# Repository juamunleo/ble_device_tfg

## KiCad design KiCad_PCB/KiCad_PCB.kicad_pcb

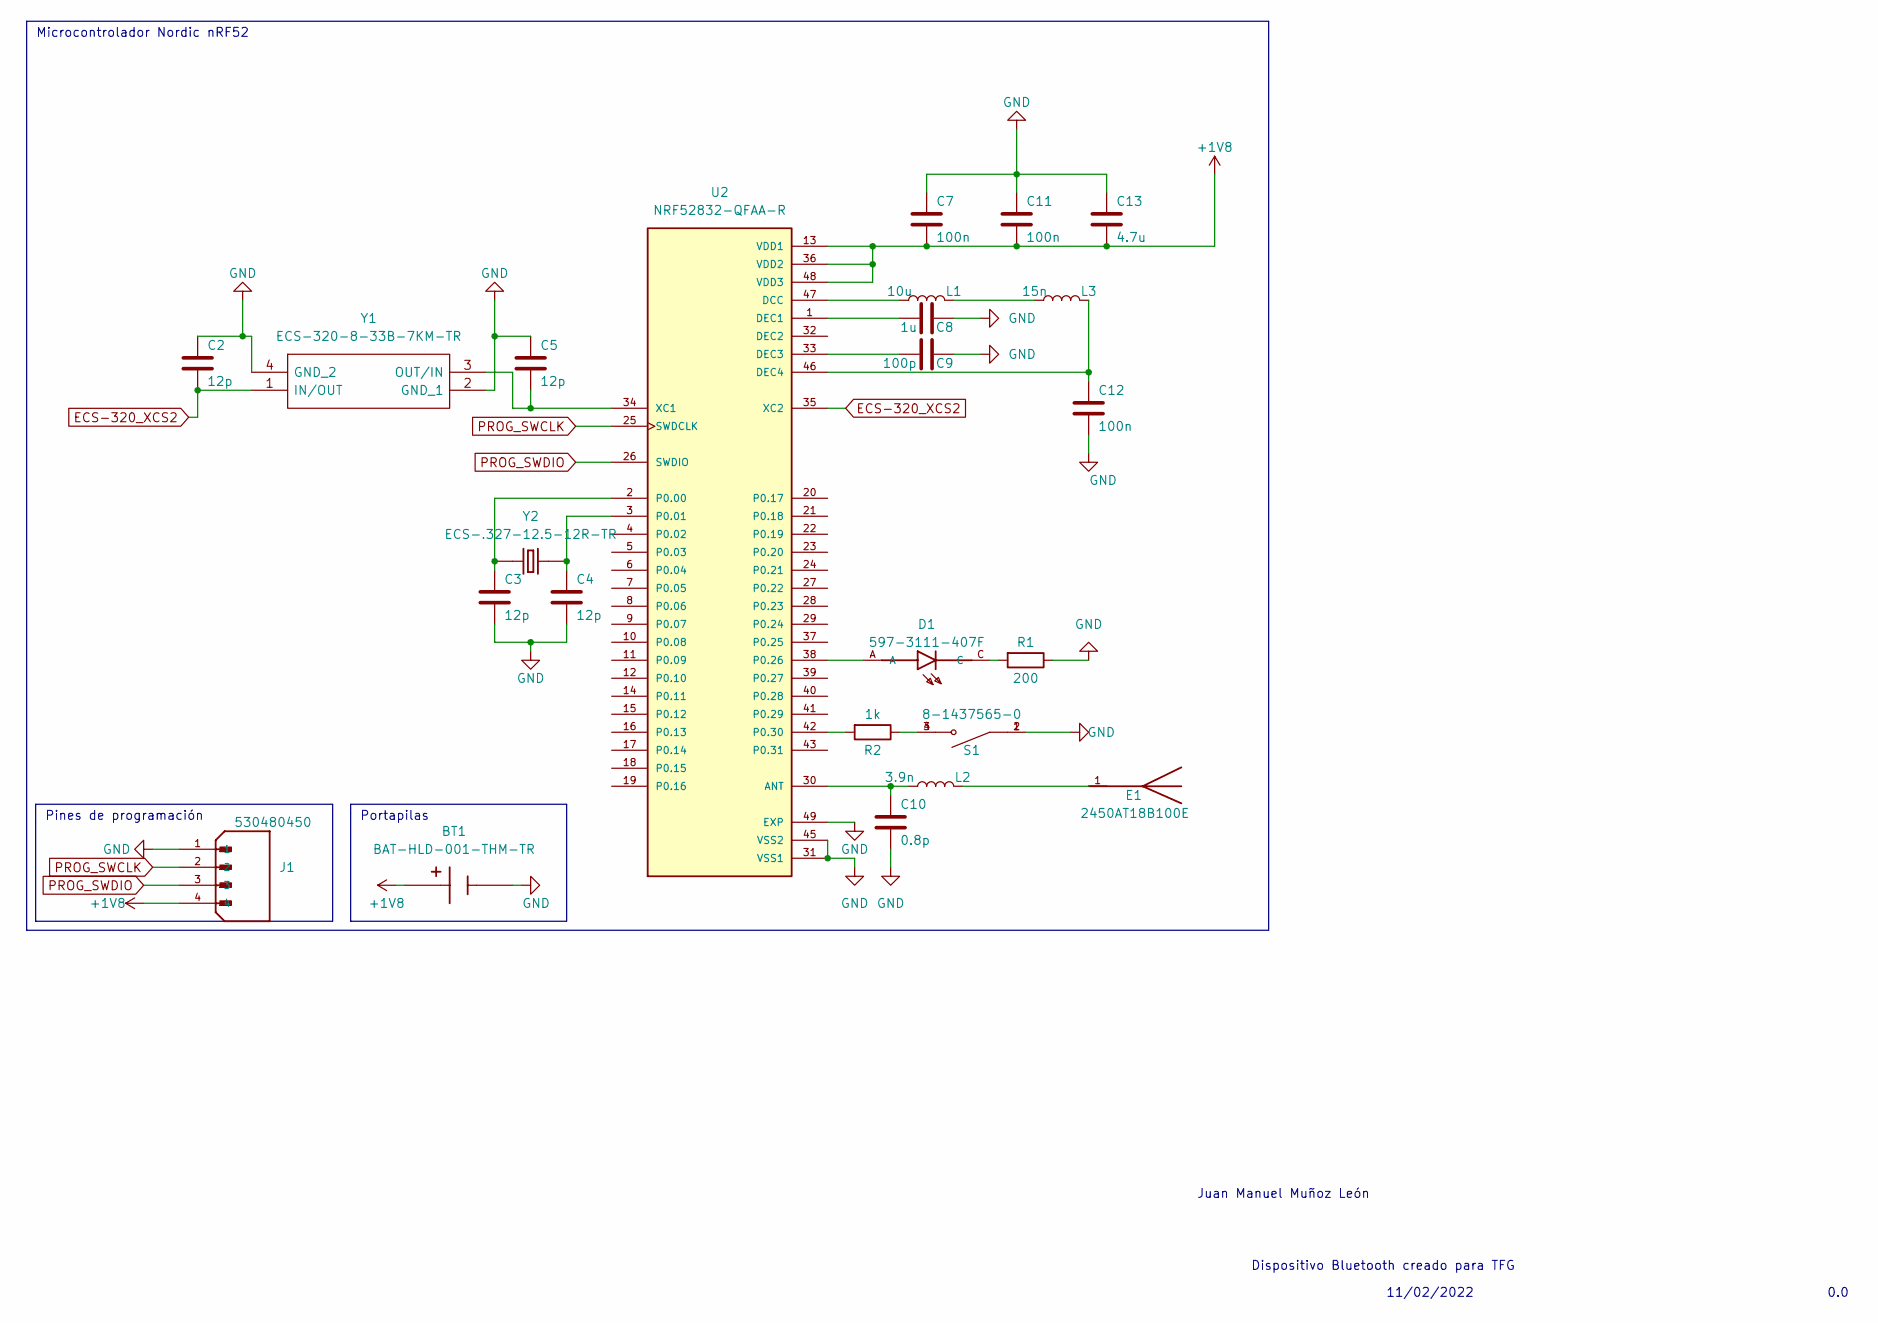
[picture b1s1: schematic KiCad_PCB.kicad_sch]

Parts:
BT1: BAT-HLD-001-THM-TR; BAT_BAT-HLD-001-THM-TR; PARTREV C
C2, C3, C4, C5: 12p; C_0603_1608Metric
C7, C11, C12: 100n; C_0603_1608Metric
C8: 1u; C_0603_1608Metric
C9: 100p; C_0603_1608Metric
C10: 0.8p; C_0603_1608Metric
C13: 4.7u; C_0603_1608Metric
D1: 597-3111-407F; LEDC3216X110N
E1: 2450AT18B100E; XDCR_2450AT18B100E; PARTREV 4.0
J1: 530480450; MOLEX_530480450; PARTREV A
L1: 10u; L_0805_2012Metric
L2: 3.9n; L_0805_2012Metric
L3: 15n; L_0805_2012Metric
R1: 200; R_0603_1608Metric
R2: 1k; R_0603_1608Metric
S1: 8-1437565-0; SW_8-1437565-0
U2: NRF52832-QFAA-R; QFN40P600X600X90-49N
Y1: ECS-320-8-33B-7KM-TR; ECS320833B7KMTR; Manufacturer_Part_Number ECS-320-8-33B-7KM-TR; Mouser Part Number 520-320-8-33B-7KM-TR
Y2: ECS-.327-12.5-12R-TR; XTAL_ECS-.327-12.5-12R-TR; PARTREV 2017

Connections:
+1V8: BT1.P1, BT1.P2, BT1.P3, BT1.P4, C7.2, C11.2, C13.2, J1.4, U2.13 (VDD1), U2.36 (VDD2), U2.48 (VDD3)
ECS-320_XCS2: C2.2, U2.35 (XC2), Y1.1 (IN/OUT)
GND: BT1.N, C2.1, C3.2, C4.2, C5.1, C7.1, C8.1, C9.1, C10.2, C11.1, C12.2, C13.1, J1.1, R1.1, S1.1, S1.2, U2.31 (VSS1), U2.45 (VSS2), U2.49 (EXP), Y1.2 (GND_1), Y1.4 (GND_2)
unnamed: C3.1, U2.2 (P0.00), Y2.1
unnamed: C4.1, U2.3 (P0.01), Y2.2
unnamed: C5.2, U2.34 (XC1), Y1.3 (OUT/IN)
unnamed: C8.2, U2.1 (DEC1)
unnamed: C9.2, U2.33 (DEC3)
unnamed: C10.1, L2.1, U2.30 (ANT)
unnamed: C12.1, L3.2, U2.46 (DEC4)
unnamed: D1.A, U2.38 (P0.26)
unnamed: D1.C, R1.2
unnamed: E1.1, L2.2
unnamed: L1.1, U2.47 (DCC)
unnamed: L1.2, L3.1
unnamed: R2.1, S1.3, S1.4
unnamed: R2.2, U2.42 (P0.30)
PROG_SWCLK: J1.2, U2.25 (SWDCLK)
PROG_SWDIO: J1.3, U2.26 (SWDIO)

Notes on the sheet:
Pines de programación
Juan Manuel Muñoz León
Microcontrolador Nordic nRF52
Dispositivo Bluetooth creado para TFG
Portapilas
11/02/2022
0.0

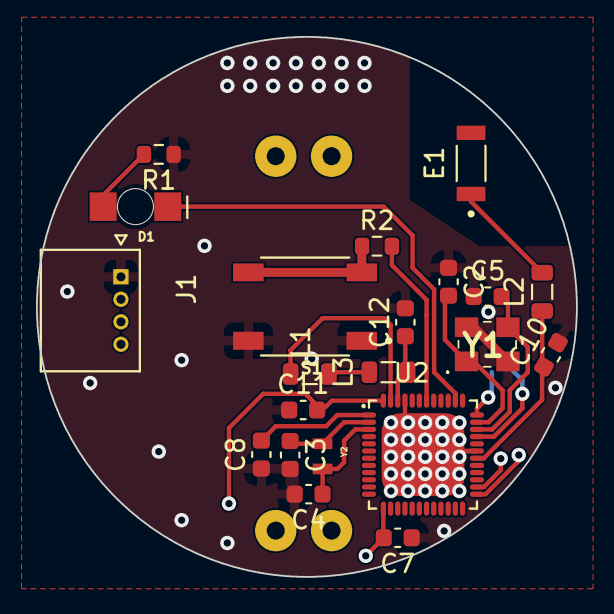
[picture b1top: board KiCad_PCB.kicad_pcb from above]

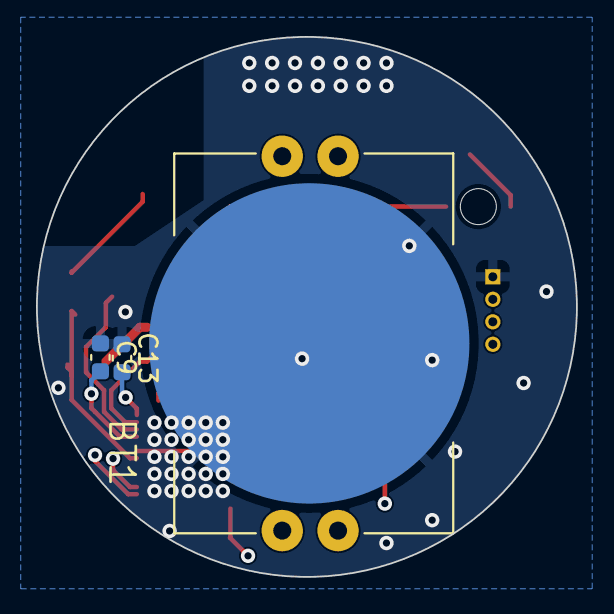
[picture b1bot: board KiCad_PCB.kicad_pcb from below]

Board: 4 copper layers, 30.0 x 30.0 mm, 24 parts (3 on the bottom side), 19 nets.

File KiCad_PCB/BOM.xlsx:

BOM
NO | Designator | Quantity | Part Number | Description | Value | Package | Comment or Link
1 | R1 | 1 |  | 200Ohms resistor | 200 | 0603
2 | R2 | 1 |  | 1kOhms resistor | 1k | 0603
3 | BT1 | 1 | BAT-HLD-001-THM-TR | Battery Holder |  |  | https://www.mouser.es/ProductDetail/Linx-Technologies/BAT-HL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
4 | C2,C3,C4,C5 | 4 |  | 12pF capacitor | 12p | 0603
5 | C7, C11, C12 | 3 |  | 0.1 uF(100nF) capacitor | 0.1u | 0603
6 | C8 | 1 |  | 1uF capacitor | 1u | 0603
7 | C19 | 1 |  | 100pF capacitor | 100p | 0603
8 | C10 | 1 |  | 0.8pF capacitor | 0.8p | 0603
9 | C13 | 1 |  | 4.7uF capacitor | 4.7u | 0603
10 | D1 | 1 | 597-3111-407F | LED |  |  | https://www.mouser.es/ProductDetail/Dialight/597-3111-407F?q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
11 | E1 | 1 | 2450AT18B100E | Bluetooth 2.45GHz Antenna |  |  | https://www.mouser.es/ProductDetail/Johanson-Technology/2450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
12 | J1 | 1 | 53048-0450 | Headers & Wire Housings |  |  | https://www.mouser.es/ProductDetail/Molex/53048-0450?qs=0lSv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
13 | L1 | 1 | CV201210-100K | 10uH inductor | 10u |  | https://www.mouser.es/ProductDetail/Bourns/CV201210-100K?qs=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
14 | L2 | 1 | CE201210-3N9J | 3.9nH inductor | 3.9n |  | https://www.mouser.es/ProductDetail/Bourns/CE201210-3N9J?qs=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
15 | L3 | 1 | CE201210-15NJ | 15nH inductor | 15n |  | https://www.mouser.es/ProductDetail/Bourns/CE201210-15NJ?qs=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
16 | S1 | 1 | FSMCTTR | Switch |  |  | https://www.mouser.es/ProductDetail/TE-Connectivity-Alcoswit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
17 | U2 | 1 | nRF52832-QFAA-R | nrf52832 SoC |  |  | https://www.mouser.es/ProductDetail/Nordic-Semiconductor/nRF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
18 | Y1 | 1 | ECS-320-8-33B-7KM-TR | Crystals 32MHz 8pF 40 ohms -20C to 70C | 32MHz |  | https://www.mouser.es/ProductDetail/ECS/ECS-320-8-33B-7KM-TR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
19 | Y2 | 1 | ECS-.327-12.5-12R-TR | Crystals 32.768kHz 12.5pF -40C +85C | 32.768KHz |  | https://www.mouser.es/ProductDetail/ECS/ECS-327-125-12R-TR?q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

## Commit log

2022-02-10 KiCad project creation
2022-02-10 Adding footprints and symbols to KiCad project
2022-02-11 KiCad schematic done
2022-02-15 PCB in progress
2022-02-22 Updated KiCad project
2022-02-22 Added System OFF
2022-03-05 Updated footprints and added battery holder on KiCad project
2022-03-06 Organising code and adding comments
2022-03-10 Added BOM template file
2022-03-10 Tutorías 10/3
2022-03-14 PCB size reduced
2022-03-16 Rewrited wrong part numbers and added links to the BOM file
2022-03-17 Tutoría Modificacion PCB
2022-03-20 Added backups to ignore file
2022-03-20 Removed backups
2022-03-21 GBR Files generated
2022-04-04 Added bond support
2022-05-21 Reorganized segger project. Added Android App project.
2022-07-10 Reworked android app. Added python post server + telegram bot. Fixed connections in segger project.
2022-07-10 Fixed to hide telegram bot token
2022-07-30 Updated bot and main.c
2022-08-01 Removed LED characteristic from Bluetooth. Now LED blinks with a timer every 500ms.
2022-08-03 Added support for battery
2022-08-03 Added BLENordicGen XML file
